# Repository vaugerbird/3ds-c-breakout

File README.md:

# 3DS-C Breakout
My take on the original 3DS-C board. Truth be told, I designed my board before doing any actual research, so I had no clue that a project like this already existed. I didn't want my work to go to waste though, so I'm opting to fork and add my board as a remix of sorts.

---

Make sure to remove and completly clean the pads for the dock pins, as my board forgos the dock and covers the pads. If you do not clean the pads the board may not sit flat.

All other warnings and instructions from the original repository also apply here, but please check BOM.ods because I have different parts designed in my board.

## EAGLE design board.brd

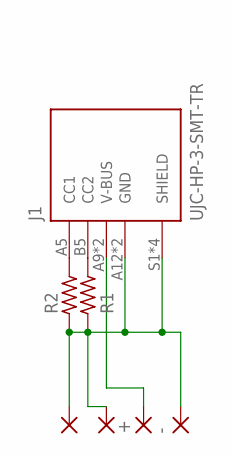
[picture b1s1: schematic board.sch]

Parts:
+: 1,6/0,9
-: 1,6/0,9
J1: UJC-HP-3-SMT-TR; CUI_UJC-HP-3-SMT-TR
PAD1, PAD4: 1,6/0,9
R1, R2: R_0402; R0402

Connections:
GND: -.1, J1.A12 (GND), J1.B12 (GND), J1.S1 (SHIELD), J1.S2 (SHIELD), J1.S3 (SHIELD), J1.S4 (SHIELD), PAD1.1, PAD4.1, R1.1, R2.1
unnamed: J1.A5 (CC1), R2.2
unnamed: J1.B5 (CC2), R1.2
VCC: +.1, J1.A9 (V-BUS), J1.B9 (V-BUS)

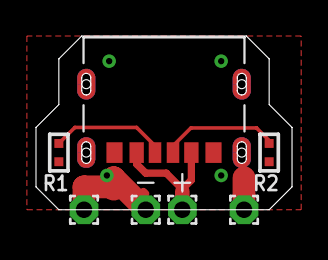
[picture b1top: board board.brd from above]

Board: 2 copper layers, 14.2 x 9.7 mm, 7 parts (0 on the bottom side), 4 nets.

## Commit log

2021-07-12 CLEAN SLATE MY GUY
2021-07-12 Add my own files
2021-07-24 Fix board layout
    After receiving my boards, I realized that the holes are lined up with the bottom of the pad instead of the middle like intended.

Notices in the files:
parts and their libraries:
rc-master-smd: Copyright (C) 2007, Bob Starr
